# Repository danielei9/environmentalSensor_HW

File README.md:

# environmentalSensor

# EnvironmentalSensor

El proyecto consta de una placa maestra donde se pueden conectar varios sensores predeterminados como temperatura, humedad, sensor de sustrato y ruido. Esta placa (Master) se comunica mediante I2C con otra placa expansión (Slave) que se comunica con un máximo de 5 sensores de cualquier tipo mediante UART (mirar especificaciones de sensores admitidos).

Una vez adquiridas las medidas de los sensores, se procesan y son enviadas mediante LORA o 4G (gsm).
En el caso de LORA: el dispositivo “Master” envía datos a un Gateway de LORA, donde mediante un Bridge realiza el cambio LORA - MQTT y enviamos los datos a la plataforma
En el caso de 4G: se envía directamente a través de MQTT.
### Master:

### Slave:

# **Contents**
- [**Project**](#firmware-hardware-module)
- [**Contents**](#contents)
- [**Pre requirements**](#pre-requirements)
- [**Getting started**](#getting-started)
- [**Project structure**](#project-structure)
- [**Firmware**](#firmware)
  - [**Master Code**](#master-code)
  - [**Slave Code**](#slave-code)
  - [**Measures**](#measures)
- [**Deployment**](#deployment)

# **Pre requirements**
This Project is being developed using `Platformio` in Visual Studio Code so you need to have being installed it and dependences. 

- Install Platformio in Visual Studio Code
# **Getting started**
1. Clone the repository
```
git clone https://github.com/ycansam/environmentalSensor_HW
```
Now you can start with the implementation of new features to comunicate with the ttgo and arduino nano

# **Project structure**
```
environmentalSensor_HW/
    ├──  doc/
    ├── Firmware/
        ├── Master/
        ├── PruebaLora/
        ├── Slave_FW_1_0
    ├── Hardware/
        ├── Master/
        ├── Slave
    ├── tests/
```

## **Enviromental devices**
Enviromental devices are the core of the application. These devices are a modular sensor hub that can contain multiple sensors according to user requirements. Multiple devices are grouped on the same gateway.
<br>
# **Firmware**
### **MASTER CODE**
#### **DEFINING CONEXION `4G` or `LORA`**
In file `Firmware/Master/main.cpp`.
* Use **#define PROTOCOL_4G** to use 4G comunication
* Use **#define PROTOCOL_LORA** to use Lora comunication
``` c++
#define PROTOCOL_4G
//#define PROTOCOL_LORA
unsigned long mill = 0;
#include <../lib/PublishersClient.h> // After defining the comunication include this libraries
#include <Wire.h>
```
##### **DEFINING 4G VARIABLES**
Change this variable acording to your SIM
In file `Firmware/Master/lib/PublishersClient.h`.
* GPRS: "orangeworld"
* GPRSUser: "orange"
* GPRSPass: "orange"
* SIMPin: null 

``` c++
#include <../lib/Protocol4G.h>
Protocol4G protocol4G(GPRS, GPRSUser, GPRSPass, SIMPin); // constructor normal
Publisher *publisher = &protocol4G;            
```

### **Setting Up the Conexion `TLS MQTT`**
##### **Configure if using `4G COMUNICATION`**
If is it needed to change the broker, username or etc on the MQTT connection you need to change this parameters in class Protocol4G in Firmware/Master/lib
``` c++
const char broker[] = "broker";
int port = port(int);
const char *username = "userBroker";
const char *password = "passBroker";
// example
// codigoPostal/ambiental/idDispositivo/
char topic[] = "46701/ambiental/1/";
const char topicSubscribed[] = "gesinen/#";
```
### **Send** `MQTT` **via 4G**
```
TOPIC /46701/ambiental/1/#
```
``` c++
// JSON MESSAGE EXAMPLE
function sendData(uint8_t *arrayData){
 ..
 String message = "{\"deviceEui\":1,\"value\": 25.222,\"type\": \"co2\", \"unit\": \"ppm\"}"
 ..
 }
```
Body:
| Name          |    Type    | Required | Description |
| ------------- |:----------:|:--------:|:-----------|
| deviceEui         | `string`   |  ✓       | DeviceEui  |
| value          | `float`   |  ✓       | Measure's value |
| unit          | `string`  |  ✓       | Measure's unit |
| type          | `string`  |  ✓       | Measure's type |
### **Request data from Slaves**
Using comunication I2C, pins using TTGO
* SDA: 21
* SCL: 22
``` c++
// Defining
SlaveController slaveController(21, 22);
```
``` c++
// Setup
// Initialize the I2C Master Comunication
slaveController.initMaster();
```
### SlaveController Fcuntions
#### Request data to a specific slave
``` c++
      byte* requestMeasuresToSlave(uint8_t, uint8_t){...}
      @param slaveAddress -> Slave address in Hexadecimal
      @param bytesToRequest -> number of Bytes
      @returns *byte -> byte array
```

``` c++
    // Example
      byte *arrayData = slaveController.requestMeasuresToSlave(0x20, bytesToRequest);
      printBytesArray(arrayData, bytesToRequest);
```

#### Scan Slaves
Scans the I2C conexion looking for slaves
``` c++
    void scanSlaves(){..}
    // prints the Slaves addresses
    // prints "Not Found" if didnt found any slave connected
```

## **SLAVE CODE**
#### Receiving commands from master
``` c++
   void receiveEvent(int bytes)
	// Se reciben eventos del maestro mediante comandos especificados en la cabezera del archivo main
```
Se inicializan los sensores y se duermen cuando se inicializa el esclavo.
El esclavo se inicializa con via I2C con una direccion
#### Inicializando el esclavo
``` c++
setup(){...

   Wire.begin(I2C_SLAVE_ADDR);
	// Se ha de definir #I2C_SLAVE_ADDR 0x20 
	// En hexadecimal
...	}
```
#### Leer comandos del maestro
``` c++
loop(){

	if (data != 0) // comprueba que el maestro ha enviado algun comando
	if (data == REQUEST_COMMAND) // dependiendo del comando ejecuta una accion u otra para posteriormente pedir un request de datos.
}
```
####Recoger las medidas de los sensores mediante semaforos
``` c++
// Recoger los datos 
void requestDataSensors();

// Ejemplo por separado
Sensor sensor1 = Sensor();
sensor1.getMeasure();
sensor1.getGasConcentration()

```

####Dormir & Despertar los sensores	
Despues de despertar y dormir cada sensor se ha de esperar 5 segundos para que vuelvan a tomar medidas y se estabilizen
``` c++
void wakeUpSensors(); // despierta los sensores
void sleepSensors(); // duerme los sensores

// Ejemplos por separado
Sensor sensor1 = Sensor();
sensor1.wakeUp();
sensor1.sleep()
```
####Recoger Informacion de Los Sensores

``` c++
void requestSensorsInformation() // recoge informacion de todos los sensores
// Ejemplo por separado
Sensor sensor1 = Sensor();
sensor1.getSensorInformation();
sensor1.getSensorType()
```

#### Envio de datos al master
Se han de enviar el array de datos con un maximo de 8 de length en cada envio para evitar errores en la lectura, Tambien se ha de hacer un flush para limpiar la Wire()
``` c++
void requestEvent()
{..}
```
# **License**
All the code in this repository is owned by [Daniel Burruchaga & Yeray Candel](https://ycansam.upv.edu.es/ & http://buchspro.com/).
Copyright © 2021, Yeray Candel. Daniel Burruchaga.
0 comments on commit cb6e9bf
Please sign in to comment.
© 2021 GitHub, Inc.
Terms
Privacy
Security
Status
Docs
Contact GitHub
Pricing
API
Training
Blog
About
Loading complete

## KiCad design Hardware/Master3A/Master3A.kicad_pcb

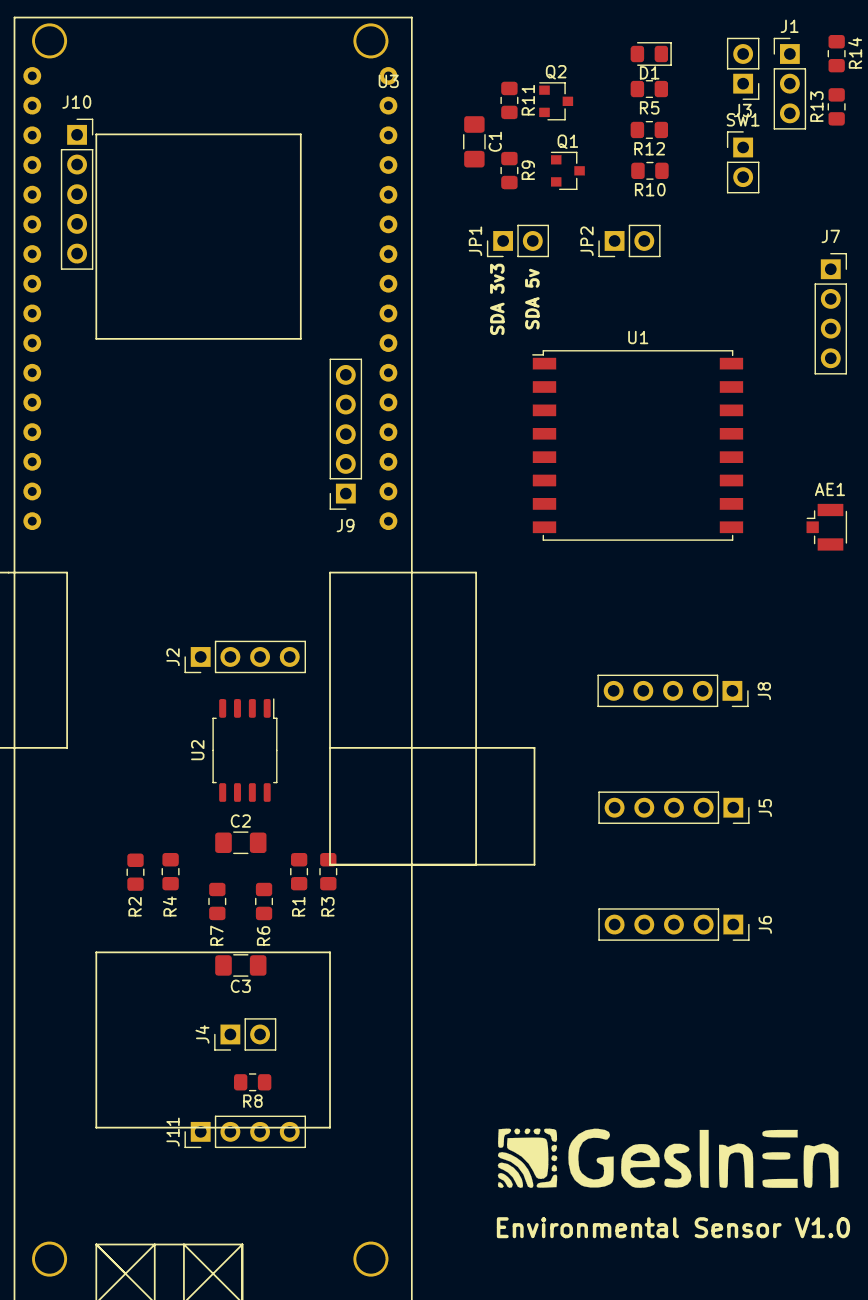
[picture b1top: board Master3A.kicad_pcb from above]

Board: 2 copper layers, 39 parts (0 on the bottom side), 33 nets, no tracks yet.

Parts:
AE1: Antenna_Chip; U.FL_Hirose_U.FL-R-SMT-1_Vertical
C1: 100nf; C_1206_3216Metric_Pad1.42x1.75mm_HandSolder
C2: 0.1uF; C_1206_3216Metric_Pad1.42x1.75mm_HandSolder
C3: 10uF; C_1206_3216Metric_Pad1.42x1.75mm_HandSolder
D1: LED; D_0805_2012Metric_Pad1.15x1.40mm_HandSolder
H1: MountingHole; GesinenLogo
J1: Conn_01x03; PinHeader_1x03_P2.54mm_Vertical
J2, J11: Conn_01x04; PinHeader_1x04_P2.54mm_Vertical
J3, J4: Conn_01x02; PinHeader_1x02_P2.54mm_Vertical
J5: SensorSuelo; PinSocket_1x05_P2.54mm_Vertical
J6: sensorRuido; PinSocket_1x05_P2.54mm_Vertical
J7: MasterSlaves; PinSocket_1x04_P2.54mm_Vertical
J8: SENSOR TEMP HUM; PinSocket_1x05_P2.54mm_Vertical
J9, J10: Conn_01x05; PinSocket_1x05_P2.54mm_Vertical
JP1, JP2: SolderJumper_2_Bridged; PinHeader_1x02_P2.54mm_Vertical
Q1, Q2: BSS138; SOT-23
R1, R2, R3, R4, R9, R10, R11, R12: 10k; R_0805_2012Metric_Pad1.15x1.40mm_HandSolder
R5, R13: 1k; R_0805_2012Metric_Pad1.15x1.40mm_HandSolder
R6, R7: 20k; R_0805_2012Metric_Pad1.15x1.40mm_HandSolder
R8: 120; R_0805_2012Metric_Pad1.15x1.40mm_HandSolder
R14: 1k7; R_0805_2012Metric_Pad1.15x1.40mm_HandSolder
SW1: SW_DIP_x01; PinHeader_1x02_P2.54mm_Vertical
U1: RFM95HW; HOPERF_RFM9XW_SMD
U2: MAX485E; SOP-8_5.28x5.23mm_P1.27mm
U3: TTGOv3SimGps; TTGo

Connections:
+3V3: C1.2, J5.1, J6.1, J8.1, Q1.1, Q2.1, R9.1, R11.1, U1.13, U3.17
+5V: C2.2, C3.2, J5.2, J6.2, J7.4, J8.2, J11.1, R1.1, R2.1, R3.1, R4.1, R5.2, R7.2, R10.1, R12.1, SW1.2, U2.8, U3.16
/A: J4.2, J5.5, J6.5, J11.3, R7.1, R8.1, U2.6
/B: J4.1, J5.4, J6.4, J11.2, R6.2, R8.2, U2.7
/GPIO2: U1.14, U3.27
/GPIO14: U1.6, U3.29
/GPIOXX: J2.2, J2.3, R2.2, R3.2, U2.2, U2.3
/MISO: U1.2, U3.8
/MOSI: U1.3, U3.7
/NSS: U1.5, U3.10
/PIN_BATT: J1.2, R13.1, R13.2, R14.2
/RX_MODBUS: J2.4, R1.2, U2.1, U3.28
/SCK: U1.4, U3.9
/SCL_3V3: JP2.1, Q2.2, R11.2, U3.5
/SCL_5V: J7.2, J8.5, JP2.2, Q2.3, R12.2
/SDA_3V3: JP1.1, Q1.2, R9.2, U3.6
/SDA_5V: J7.1, J8.4, JP1.2, Q1.3, R10.2
/TX_MODBUS: J2.1, R4.2, U2.4, U3.30
GND: AE1.2, C1.1, C2.1, C3.1, D1.1, J1.1, J5.3, J6.3, J7.3, J8.3, J11.4, R6.1, R14.1, U1.1, U1.8, U1.10, U2.5, U3.18
unnamed: AE1.1, U1.9
unnamed: D1.2, J3.2
unnamed: J1.3, SW1.1
unnamed: J3.1, R5.1
unnamed: J9.1, U3.15
unnamed: J9.2, U3.14
unnamed: J9.3, U3.13
unnamed: J9.4, U3.12
unnamed: J9.5, U3.11
unnamed: J10.1, U3.19
unnamed: J10.2, U3.20
unnamed: J10.3, U3.21
unnamed: J10.4, U3.22
unnamed: J10.5, U3.23

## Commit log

2021-11-03 Init Publisher y Joined creados en 4G. Arreglados bugs clase Publisher
2021-11-03 Añadido protocolo MQTT de envio de datos y Recepcion de datos.
2021-11-04 Añadidos comentarios
2021-11-04 Lora
2021-11-04 Organizada Estructura
2021-11-04 Hardware
2021-11-04 Diseños Añadidos 4G y Publicador
2021-11-04 Hardware update
2021-11-09 Cambiada la placa del esclavo
2021-11-09 Creado SlaveController
2021-11-09 Optimizacion de la clase Publicadores + Main + creado PublicadoresClient y Utils.h
2021-11-12 TLS MQTT Añadido
2021-11-16 Optimized Slave Controller
    Working commit I2C
2021-11-17 UpdateLora
2021-11-22 Primer test software serial
    Funcionando con 2 arduinos.
2021-11-23 SensorUART class implementada
2021-11-23 getType y getMeasure Implementados
    Añadidos testUart, y se han testeado 5 UARTS
2021-11-24 Solved Error Writing Data to I2C with UART (Simulated)
2021-11-24 Update finished Hardware
2021-11-25 Slave Funcinando por Commandos
2021-11-25 Update Modbus
2021-11-25 test
2021-11-25 CMJU Library
2021-11-26 ModBuss Implementado
2021-11-26 Squashed commit of the following:
    commit dc66c705c26bb8546bf42e4e2412be2f97287fa4
    Author: Yeray Candel <ycansam@epsg.upv.es>
    Date: Fri Nov 26 01:18:12 2021 +0100
    ModBuss Implementado
    commit e472c0fb496fb5f31392eb650849038dd407901c
    Author: Daniel Burruchaga <dbs99@hotmail.com>
2021-11-26 Hard
2021-11-26 Ota 100%
2021-11-26 Ota 100
2021-11-26 v1.2
2021-11-26 v1.2.1
    Fix Securty
2021-11-29 OTA v1.0
    La actualizacion over the air ya funciona comprobado (Sin clases)
2021-12-01 v1.0 GPS
2021-12-01 v1.0.1
    Todos los cambios comprobados y funcionando con la sim 7000G
2021-12-01 Example GPS && COmentarios
2021-12-01 Corrected defined error
2021-12-01 Example use 4G
2021-12-01 SlaveController Example
2021-12-02 updateOTA
2021-12-13 Example lora
2021-12-13 Examples
2021-12-14 example ota update add
2021-12-14 Lora Example
2021-12-14 Examples Modbus
2021-12-14 Cambiado Nano a Pro Mini
2021-12-14 Slave Reading Slave
2021-12-14 Sensores leidos con la libreria
2021-12-15 Los sensores ya se leen correctamente con peticiones del master
2021-12-15 Sensores Duermiendo Despertando Leyendo y Despertando
2021-12-16 Los Sensores se duermen, se despiertan, leen y se duermen con el master
2021-12-16 Test Lora Publisher
2021-12-16 comit 4 de la mañana casi 5
2021-12-16 Si no hubiese sido por buchu hubiese tardado 2 horas antes
2021-12-16 Test TODO OK
2021-12-16 Master recibe peticiones MQTT
2021-12-16 Update OTA to MASTER working (Culpa de yeray que no funcione)
2021-12-16 add working Sensor Modbus, floorSensor, noiseSensor
    Esta funcionando Lora, OTA Update , Modbus, Recoger Datos slave, enviarlos por 4g
2021-12-16 Protocolo4G Y Lora Working
    Funcionan al intercambiar variables
2021-12-17 Maestro lee el tipo de sensor y las unidades
2021-12-17 Maestro ya lee los ppms
2021-12-17 Los sensores se actualizan al intercambiarse en cualquier momento
2021-12-17 Linking working
2021-12-17 Updated SendData
2021-12-17 Fix send data
2021-12-17 TODO ok
2021-12-17 v1.4
2021-12-17 El maestro lee hasta un maximo de 127 esclavos
    Envia las mediciones de cada 1 de los esclavos por mqtt en 4G
2021-12-18 Refactorizado Slave
2021-12-19 Slave Master. Actualizado comentarios y refactorizado
2021-12-19 SYNCRONIZED WORKING
    Ahora se vincula con la plataforma
2021-12-19 Link Controller SYNC with web working
2021-12-19 Arreglado OTA UPDATE y Refactorizado maestro
2021-12-19 LINK OK
2021-12-19 Fix Slave Measures Analyzer
2021-12-19 upds
2021-12-19 send data OK
2021-12-19 deveui
2021-12-19 Revert "deveui"
    This reverts commit fc2b0a7c7da43b2195d98d1f5521609a95d4a1f0.
2021-12-19 namedevice
2022-01-13 doc tecnica
2022-01-14 upd doc
